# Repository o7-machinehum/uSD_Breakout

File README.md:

uSD Breakout
=========
Micro SD (uSD) Breakout is a device to be inserted into a micro SD card slot to breakout the pins. This project is designed for the pinebook. But theoretically can be used for any uSD card slot.

Additional Components
----------------
| Part Number   | Digi Part Number           | Desc.                                       |
| ------------- |----------------------------| --------------------------------------------|
| MCP23S17T-E/SS| MCP23S17T-E/SSCT-ND        | I/O Expander 16 SPI 10MHz 28-SSOP           |
| RTL8710       | N/A                        | Wifi module w/ ARM Cortex M3                |

Notes
-----
-PCB thickness - 0.6mm

Walker (Machinehum)

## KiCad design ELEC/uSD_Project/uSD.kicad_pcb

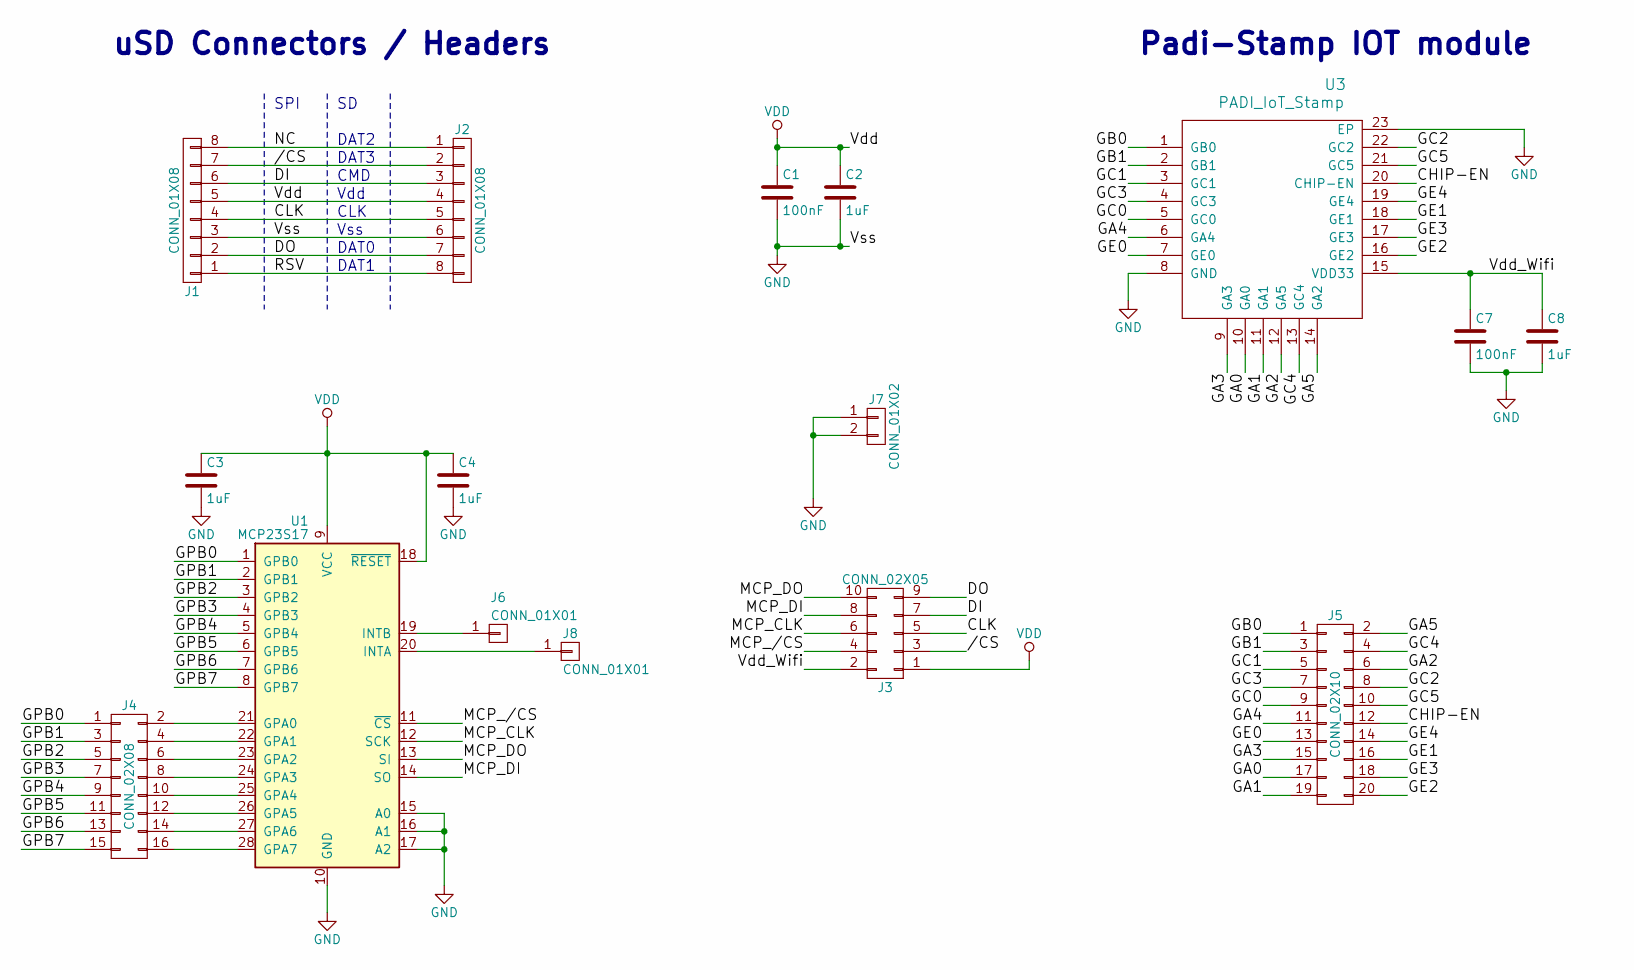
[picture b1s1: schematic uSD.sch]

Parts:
C1, C7: 100nF; C_0805_HandSoldering
C2, C3, C4, C8: 1uF; C_0805_HandSoldering
J1: CONN_01X08; Pin_Header_Straight_1x08_Pitch2.54mm
J2: CONN_01X08; uSD
J3: CONN_02X05; Pin_Header_Straight_2x05_Pitch1.27mm
J4: CONN_02X08; Pin_Header_Angled_2x08_Pitch2.54mm
J5: CONN_02X10; Pin_Header_Angled_2x10_Pitch2.54mm
J6, J8: CONN_01X01; 10mil_Via
J7: CONN_01X02; Pin_Header_Straight_1x02_Pitch2.54mm
U1: MCP23S17; SSOP-28_5.3x10.2mm_Pitch0.65mm; Part Number MCP23S17T-E/SS
U3: PADI_IoT_Stamp

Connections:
//CS: J1.7, J2.2, J3.3
/CHIP-EN: J5.12, U3.20 (CHIP-EN)
/CLK: J1.4, J2.5, J3.5
/DI: J1.6, J2.3, J3.7
/DO: J1.2, J2.7, J3.9
/GA0: J5.17, U3.10 (GA0)
/GA1: J5.19, U3.11 (GA1)
/GA2: J5.6, U3.12 (GA5)
/GA3: J5.15, U3.9 (GA3)
/GA4: J5.11, U3.6 (GA4)
/GA5: J5.2, U3.14 (GA2)
/GB0: J5.1, U3.1 (GB0)
/GB1: J5.3, U3.2 (GB1)
/GC0: J5.9, U3.5 (GC0)
/GC1: J5.5, U3.3 (GC1)
/GC2: J5.8, U3.22 (GC2)
/GC3: J5.7, U3.4 (GC3)
/GC4: J5.4, U3.13 (GC4)
/GC5: J5.10, U3.21 (GC5)
/GE0: J5.13, U3.7 (GE0)
/GE1: J5.16, U3.18 (GE1)
/GE2: J5.20, U3.16 (GE2)
/GE3: J5.18, U3.17 (GE3)
/GE4: J5.14, U3.19 (GE4)
/GPB0: J4.1, U1.1 (GPB0)
/GPB1: J4.3, U1.2 (GPB1)
/GPB2: J4.5, U1.3 (GPB2)
/GPB3: J4.7, U1.4 (GPB3)
/GPB4: J4.9, U1.5 (GPB4)
/GPB5: J4.11, U1.6 (GPB5)
/GPB6: J4.13, U1.7 (GPB6)
/GPB7: J4.15, U1.8 (GPB7)
/MCP_/CS: J3.4, U1.11 (~CS)
/MCP_CLK: J3.6, U1.12 (SCK)
/MCP_DI: J3.8, U1.14 (SO)
/MCP_DO: J3.10, U1.13 (SI)
/NC: J1.8, J2.1
/RSV: J1.1, J2.8
/Vdd_Wifi: C7.1, C8.1, J3.2, U3.15 (VDD33)
GND: C1.2, C2.2, C3.2, C4.2, C7.2, C8.2, J1.3, J2.6, J7.1, J7.2, U1.10 (GND), U1.15 (A0), U1.16 (A1), U1.17 (A2), U3.8 (GND), U3.23 (EP)
unnamed: J4.2, U1.21 (GPA0)
unnamed: J4.4, U1.22 (GPA1)
unnamed: J4.6, U1.23 (GPA2)
unnamed: J4.8, U1.24 (GPA3)
unnamed: J4.10, U1.25 (GPA4)
unnamed: J4.12, U1.26 (GPA5)
unnamed: J4.14, U1.27 (GPA6)
unnamed: J4.16, U1.28 (GPA7)
unnamed: J6.1, U1.19 (INTB)
unnamed: J8.1, U1.20 (INTA)
VDD: C1.1, C2.1, C3.1, C4.1, J1.5, J2.4, J3.1, U1.9 (VCC), U1.18 (~RESET)

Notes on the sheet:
SPI
DAT2
DAT3
CMD
Vdd
CLK
Vss
DAT0
DAT1
uSD Connectors / Headers
Padi-Stamp IOT module

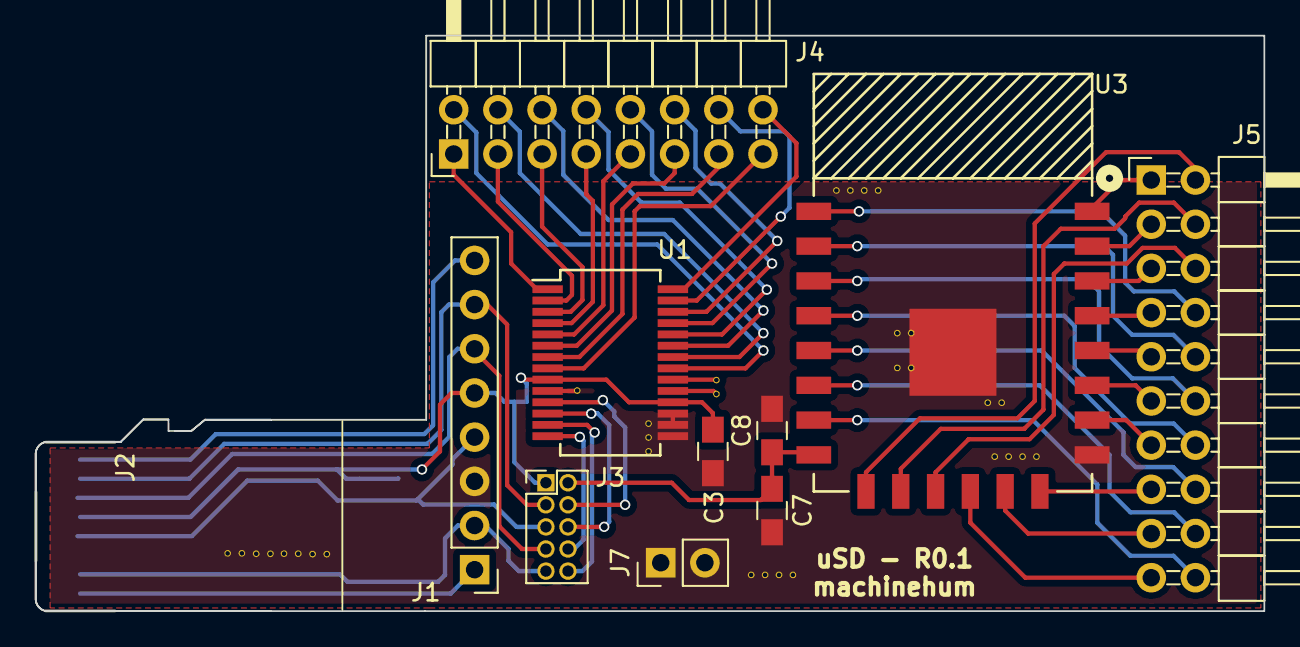
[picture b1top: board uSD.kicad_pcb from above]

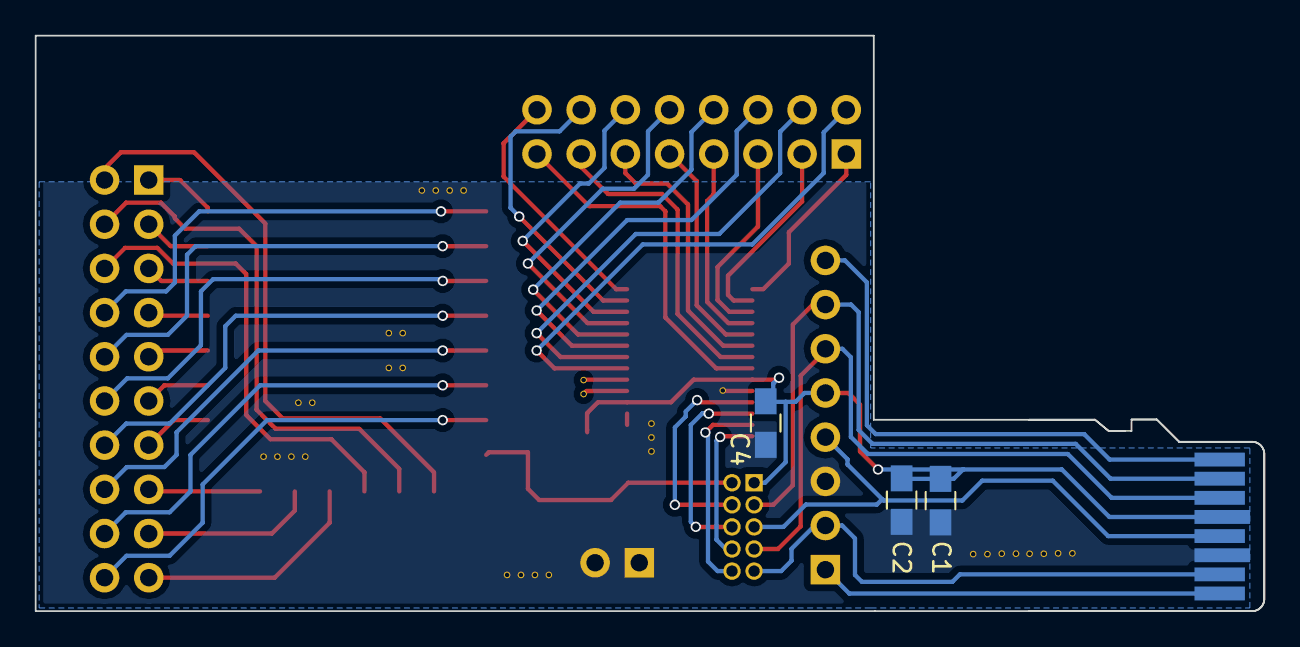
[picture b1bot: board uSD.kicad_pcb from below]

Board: 2 copper layers, 70.6 x 33.1 mm, 16 parts (3 on the bottom side), 51 nets.

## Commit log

2017-08-30 Init
2017-08-30 Formatting
2017-08-30 More formattings
2017-08-30 1. Added parts lib 2. Started schematic, dropped in both shift registers
2017-09-01 Added uSD outline
2017-09-01 - Schematic capture - Creation of uSD part
2017-09-01 Added pictures
2017-09-06 Added padi stamp to project, moved some parts around, added pin headers, fixed net labels for shift reg etc...
2017-09-07 Changed out shift registers, started and almost completed routing
2017-09-09 Finished layout, all the uSD pins are backwards. Last ECO
2017-09-09 readme mod
2017-09-10 Flipped uSD connector so it's proper, generated gerbers, ordered PCBs!
2017-09-12 Regenerated gerbers
2017-09-13 Added zip file
2017-09-20 Changed readme, uploaded some images
2017-10-15 Gerbers different?
